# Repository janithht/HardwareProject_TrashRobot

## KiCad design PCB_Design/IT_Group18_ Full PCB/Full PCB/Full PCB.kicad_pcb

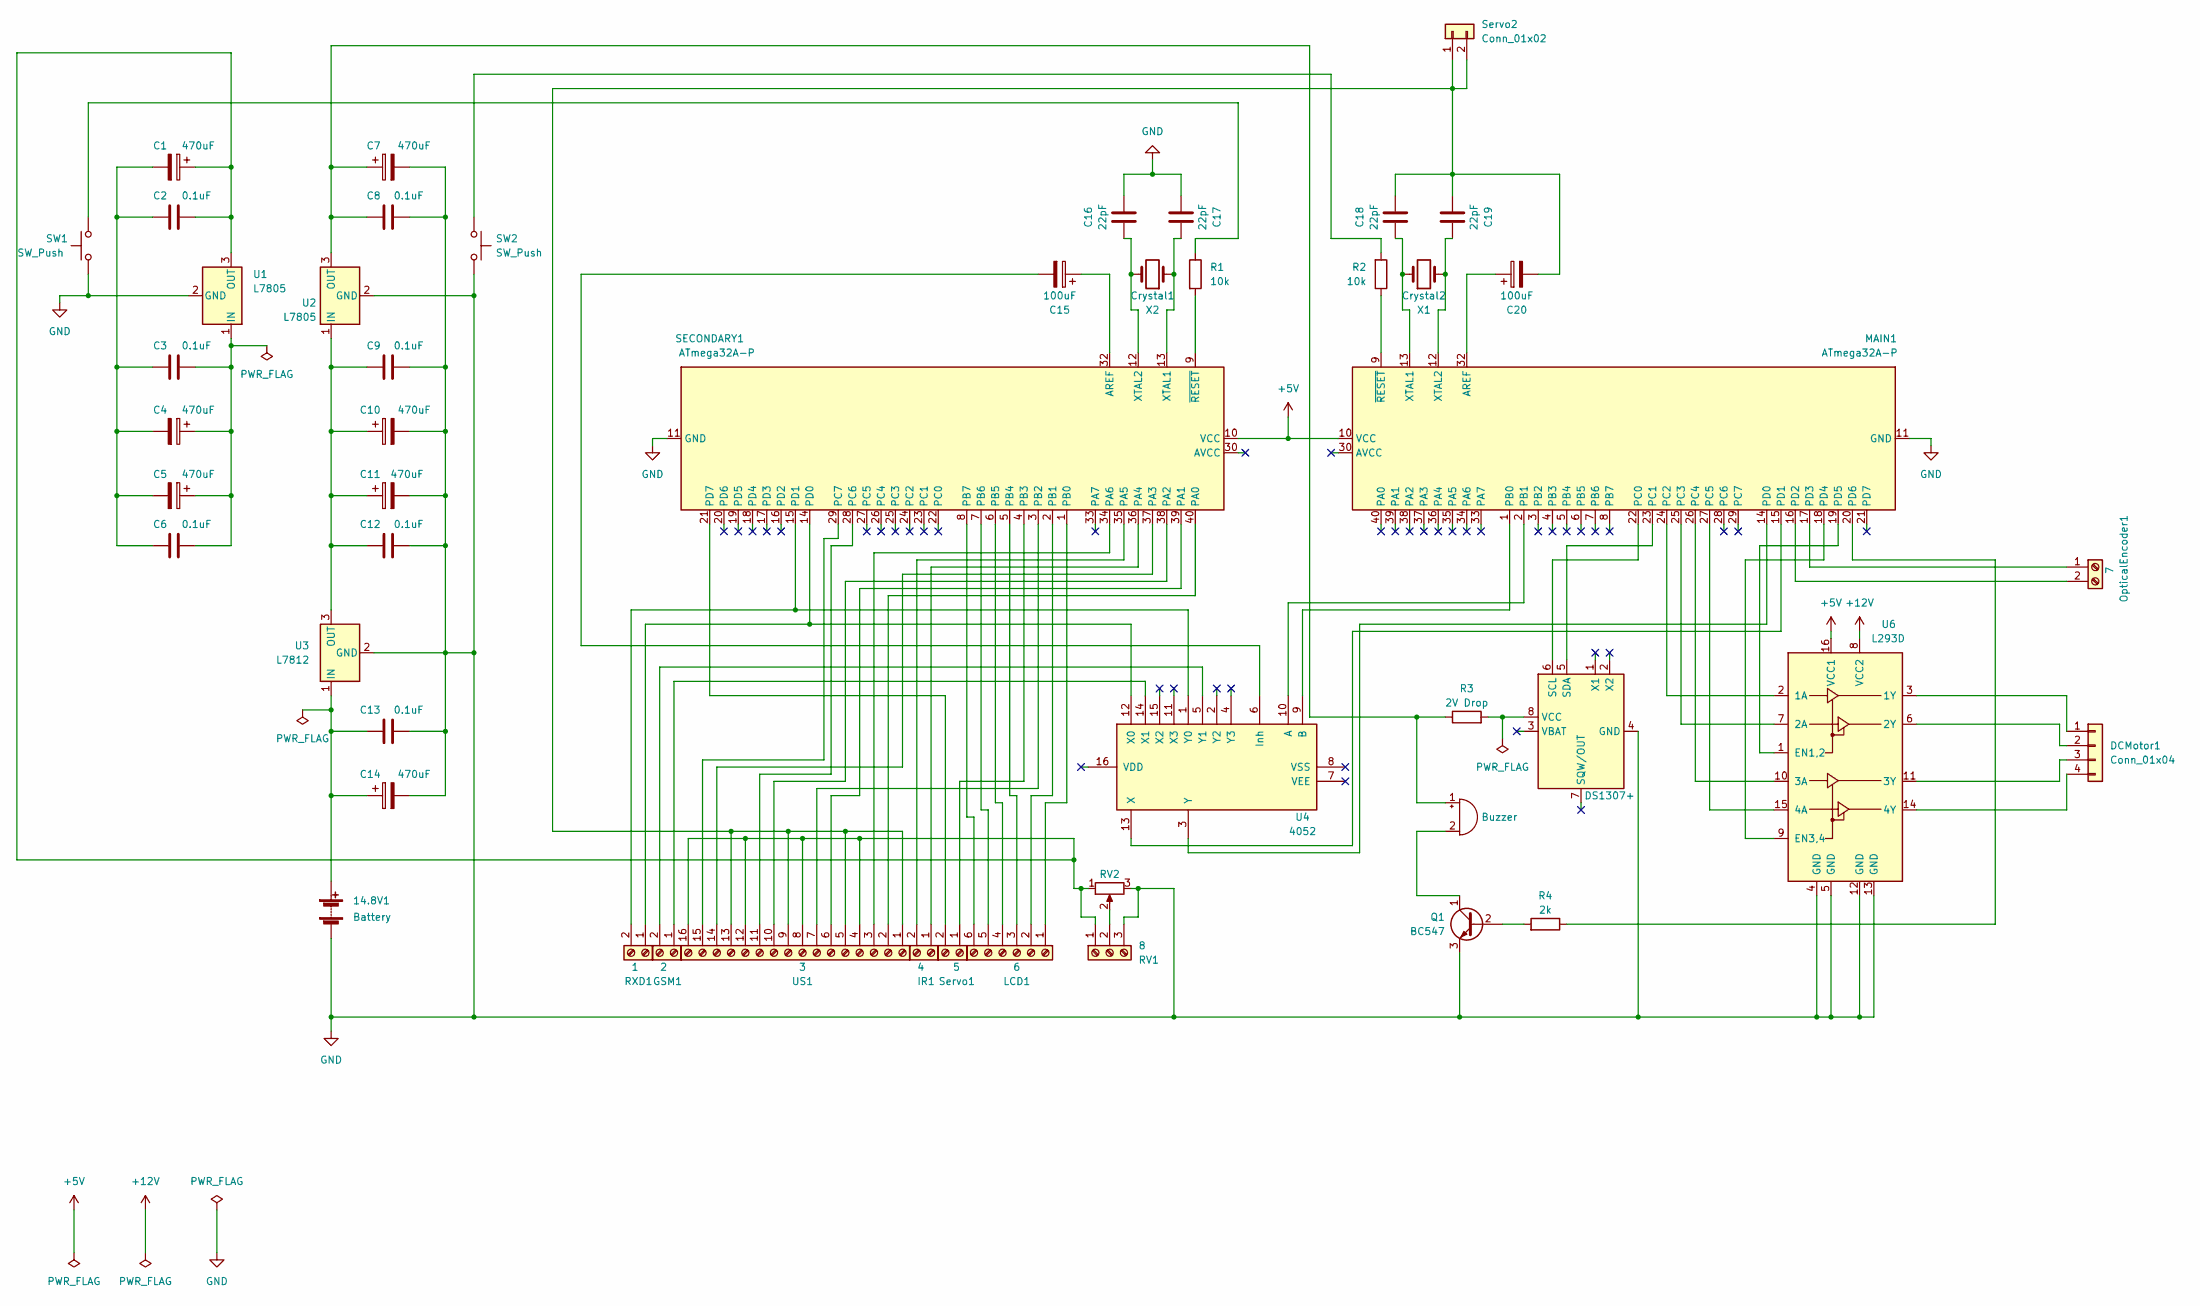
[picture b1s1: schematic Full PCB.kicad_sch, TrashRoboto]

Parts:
14.8V1: Battery; BatteryHolder_Bulgin_BX0036_1xC
BZ1: Buzzer; Buzzer_12x9.5RM7.6
C1, C4, C5, C7, C10, C11, C14: 470uF; CP_Radial_D5.0mm_P2.50mm
C2, C3, C6, C8, C9, C12, C13: 0.1uF; CP_Radial_D5.0mm_P2.50mm
C15, C20: 100uF; CP_Radial_D5.0mm_P2.50mm
C16, C17, C18, C19: 22pF; CP_Radial_D5.0mm_P2.50mm
Crystal1: X2; Crystal_HC52-U_Vertical
Crystal2: X1; Crystal_HC52-U_Vertical
DCMotor1: Conn_01x04; PinSocket_1x04_P2.54mm_Vertical
GSM1: 2; TerminalBlock_Dinkle_DT-55-B01X-02_P10.00mm
IR1: 4; TerminalBlock_Dinkle_DT-55-B01X-02_P10.00mm
LCD1: 6; TerminalBlock_Dinkle_DT-55-B01X-06_P10.00mm
MAIN1: ATmega32A-P; DIP-40_W15.24mm
OpticalEncoder1: 7; TerminalBlock_Dinkle_DT-55-B01X-02_P10.00mm
Q1: BC547; TO-92_Inline
R1, R2: 10k; R_Axial_DIN0207_L6.3mm_D2.5mm_P10.16mm_Horizontal
R3: 2V Drop; R_Axial_DIN0207_L6.3mm_D2.5mm_P10.16mm_Horizontal
R4: 2k; R_Axial_DIN0207_L6.3mm_D2.5mm_P10.16mm_Horizontal
RV1: 8; TerminalBlock_Dinkle_DT-55-B01X-03_P10.00mm
RV2: R_Potentiometer; Potentiometer_Runtron_RM-065_Vertical
RXD1: 1; TerminalBlock_Dinkle_DT-55-B01X-02_P10.00mm
SECONDARY1: ATmega32A-P; DIP-40_W15.24mm
SW1, SW2: SW_Push; SW_PUSH_6mm_H5mm
Servo1: 5; TerminalBlock_Dinkle_DT-55-B01X-02_P10.00mm
Servo2: Conn_01x02; PinSocket_1x02_P2.54mm_Vertical
U1, U2: L7805; TO-220-3_Vertical
U3: L7812; TO-220-3_Vertical
U4: 4052; DIP-16_W7.62mm
U5: DS1307+; DIP-8_W7.62mm
U6: L293D; DIP-16_W7.62mm
US1: 3; TerminalBlock_Dinkle_DT-55-B01X-16_P10.00mm

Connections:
+5V: MAIN1.10 (VCC), SECONDARY1.10 (VCC), U6.16 (VCC1)
+12V: U6.8 (VCC2)
GND: 14.8V1.2 (-), C7.2, C8.2, C9.2, C10.2, C11.2, C12.2, C13.2, C14.2, C16.2, C17.1, MAIN1.11 (GND), MAIN1.31 (GND), Q1.3 (E), RV1.3, RV2.3, SECONDARY1.11 (GND), SECONDARY1.31 (GND), SW1.2, SW2.2, U1.2 (GND), U2.2 (GND), U3.2 (GND), U5.4 (GND), U6.4 (GND), U6.5 (GND), U6.12 (GND), U6.13 (GND)
unnamed: 14.8V1.1 (+), C13.1, C14.1, U3.1 (IN)
unnamed: BZ1.1 (-), C7.1, C8.1, R3.1, U2.3 (OUT)
unnamed: BZ1.2 (+), Q1.1 (C)
unnamed: C1.2, C2.2, C3.2, C4.2, C5.2, C6.2
unnamed: C3.1, C4.1, C5.1, C6.1, U1.1 (IN)
unnamed: C9.1, C10.1, C11.1, C12.1, U2.1 (IN), U3.3 (OUT)
unnamed: C15.1, SECONDARY1.32 (AREF)
unnamed: C15.2, U4.6 (Inh)
unnamed: C16.1, Crystal1.2, SECONDARY1.12 (XTAL2)
unnamed: C17.2, Crystal1.1, SECONDARY1.13 (XTAL1)
unnamed: C18.1, C19.2, C20.2, Servo2.1, Servo2.2, US1.1, US1.5, US1.9, US1.13
unnamed: C18.2, Crystal2.1, MAIN1.13 (XTAL1)
unnamed: C19.1, Crystal2.2, MAIN1.12 (XTAL2)
unnamed: C20.1, MAIN1.32 (AREF)
unnamed: DCMotor1.1, U6.3 (1Y)
unnamed: DCMotor1.2, U6.6 (2Y)
unnamed: DCMotor1.3, U6.11 (3Y)
unnamed: DCMotor1.4, U6.14 (4Y)
unnamed: GSM1.1, U4.14 (X1)
unnamed: GSM1.2, U4.5 (Y1)
unnamed: IR1.1, SECONDARY1.36 (PA4)
unnamed: IR1.2, SECONDARY1.35 (PA5)
unnamed: MAIN1.1 (PB0), U4.9 (B)
unnamed: MAIN1.2 (PB1), U4.10 (A)
unnamed: MAIN1.9 (~RESET), R2.1
unnamed: MAIN1.14 (PD0), U4.3 (Y)
unnamed: MAIN1.15 (PD1), U4.13 (X)
unnamed: MAIN1.16 (PD2), OpticalEncoder1.2
unnamed: MAIN1.17 (PD3), OpticalEncoder1.1
unnamed: MAIN1.18 (PD4), U6.9 (EN3,4)
unnamed: MAIN1.19 (PD5), U6.1 (EN1,2)
unnamed: MAIN1.20 (PD6), R4.1
unnamed: MAIN1.22 (PC0), U5.6 (SCL)
unnamed: MAIN1.23 (PC1), U5.5 (SDA)
unnamed: MAIN1.24 (PC2), U6.2 (1A)
unnamed: MAIN1.25 (PC3), U6.7 (2A)
unnamed: MAIN1.26 (PC4), U6.10 (3A)
unnamed: MAIN1.27 (PC5), U6.15 (4A)
unnamed: Q1.2 (B), R4.2
unnamed: R1.1, SW1.1
unnamed: R1.2, SECONDARY1.9 (~RESET)
unnamed: R2.2, SW2.1
unnamed: R3.2, U5.8 (VCC)
unnamed: C1.1, C2.1, RV1.1, RV2.1, U1.3 (OUT), US1.4, US1.8, US1.12, US1.16
unnamed: RV1.2, RV2.2
unnamed: RXD1.1, SECONDARY1.14 (PD0), U4.12 (X0)
unnamed: RXD1.2, SECONDARY1.15 (PD1), U4.1 (Y0)
unnamed: LCD1.1, SECONDARY1.1 (PB0)
unnamed: LCD1.2, SECONDARY1.2 (PB1)
unnamed: SECONDARY1.3 (PB2), US1.7
unnamed: SECONDARY1.4 (PB3), Servo1.1
unnamed: LCD1.3, SECONDARY1.5 (PB4)
unnamed: LCD1.4, SECONDARY1.6 (PB5)
unnamed: LCD1.5, SECONDARY1.7 (PB6)
unnamed: LCD1.6, SECONDARY1.8 (PB7)
unnamed: SECONDARY1.21 (PD7), Servo1.2
unnamed: SECONDARY1.28 (PC6), US1.11
unnamed: SECONDARY1.29 (PC7), US1.15
unnamed: SECONDARY1.34 (PA6), US1.3
unnamed: SECONDARY1.37 (PA3), US1.14
unnamed: SECONDARY1.38 (PA2), US1.10
unnamed: SECONDARY1.39 (PA1), US1.6
unnamed: SECONDARY1.40 (PA0), US1.2

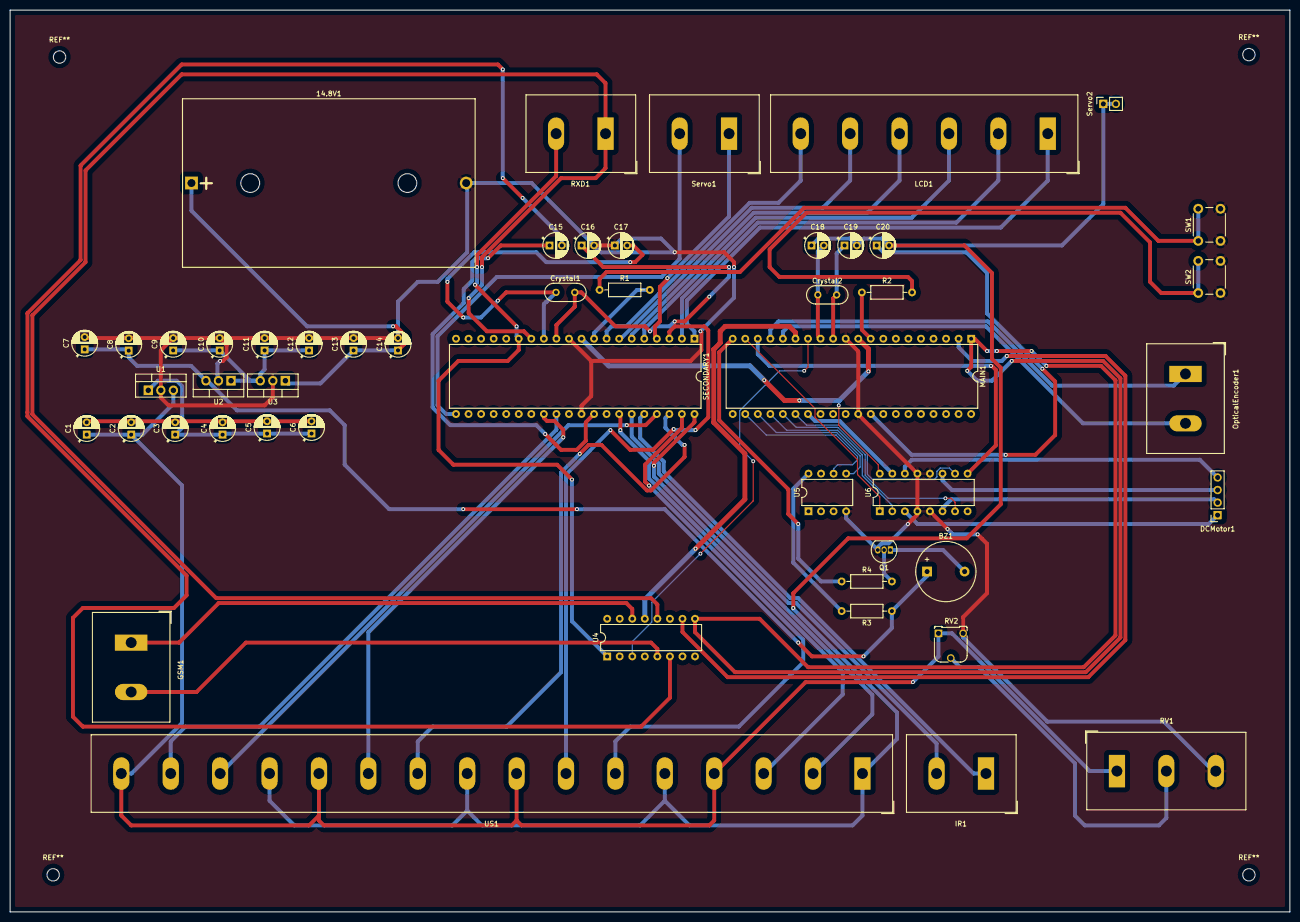
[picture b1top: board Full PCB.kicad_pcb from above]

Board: 2 copper layers, 259.0 x 182.5 mm, 50 parts (0 on the bottom side), 65 nets.

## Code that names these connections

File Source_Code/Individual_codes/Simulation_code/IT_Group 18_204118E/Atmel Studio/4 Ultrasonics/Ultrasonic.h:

#ifndef ULTRASONIC_H_
#define ULTRASONIC_H_

#define US1_TRIG_POS PA0         // Trigger pin on PA0
#define US1_ECHO_POS PA6         // Echo pin on PA6

#define US3_TRIG_POS PA2         // Trigger pin on PA2
#define US3_ECHO_POS PC6         // Echo pin on PA6

#define US2_TRIG_POS PA1        // Trigger pin on PA1
#define US2_ECHO_POS PB2         // Echo pin on PB2

#define US4_TRIG_POS PA3        // Trigger pin on PA3
#define US4_ECHO_POS PC7         // Echo pin on PC7

#define	US_NO_OBSTACLE	-2

// Function Prototypes
void HCSR04Init();
void HCSR04Trigger1();
void HCSR04Trigger2();
uint16_t GetPulseWidth1();
uint16_t GetPulseWidth2();
void HCSR04Trigger3();
void HCSR04Trigger4();
uint16_t GetPulseWidth3();
uint16_t GetPulseWidth4();

void HCSR04Init()						// Ultrasonic sensor initialization
{
	DDRA|=(1<<US1_TRIG_POS);			// Trigger pin as output
	DDRA|=(1<<US2_TRIG_POS);
	DDRA|=(1<<US3_TRIG_POS);			// Trigger pin as output
	DDRA|=(1<<US4_TRIG_POS);
}

void HCSR04Trigger1()					// Trigger pulse
{
	PORTA |= (1<<US1_TRIG_POS);		//high
	_delay_us(15);						//wait 15uS
	PORTA &= ~(1<<US1_TRIG_POS);		//low
}

void HCSR04Trigger2()					// Trigger pulse
{
	PORTA |= (1<<US2_TRIG_POS);		//high
	_delay_us(15);						//wait 15uS
	PORTA &= ~(1<<US2_TRIG_POS);		//low
}

uint16_t GetPulseWidth1()				// Measure the pulse duration
{
	uint32_t i,result;

	for(i=0;i<600000;i++)				// Checking whether ultrasonic sensor is working
	{
		if(!(PINA & (1<<US1_ECHO_POS)))
		continue;						//Line is still low
		else
		break;							//High edge detected
	}

	
	TCCR1A=0X00;
	TCCR1B=(1<<CS11);					// Resolution of the timer
	TCNT1=0x00;							// Start counting time

	for(i=0;i<600000;i++)				// Almost 40 milliseconds
	{
		if(PINA & (1<<US1_ECHO_POS))
		{
			if(TCNT1 > 60000)
			break;						// No object in the range
			else
			continue;
		}
		else
		break;
	}

	if(i==600000)
	return US_NO_OBSTACLE;				//Time out

	result=TCNT1;						//Falling edge found
	
	TCCR1B=0x00;						//Stop Timer

	if(result > 60000)
	return US_NO_OBSTACLE;				//No obstacle
	else
	return (result>>1);
}

uint16_t GetPulseWidth2()				// Measure the pulse duration
{
	uint32_t i,result;

	for(i=0;i<600000;i++)				// Checking whether ultrasonic sensor is working
	{
		if(!(PINB & (1<<US2_ECHO_POS)))
		continue;						//Line is still low
		else
		break;							//High edge detected
	}

	
	TCCR1A=0X00;
	TCCR1B=(1<<CS11);					// Resolution of the timer
	TCNT1=0x00;							// Start counting time

	for(i=0;i<600000;i++)				// Almost 40 milliseconds
	{
		if(PINB & (1<<US2_ECHO_POS))
		{
			if(TCNT1 > 60000)
			break;						// No object in the range
			else
			continue;
		}
		else
		break;
	}

	if(i==600000)
	return US_NO_OBSTACLE;				//Time out

	result=TCNT1;						//Falling edge found
	
	TCCR1B=0x00;						//Stop Timer

	if(result > 60000)
	return US_NO_OBSTACLE;				//No obstacle
	else
	return (result>>1);
}


void HCSR04Trigger3()					// Trigger pulse
{
	PORTA |= (1<<US3_TRIG_POS);		//high
	_delay_us(15);						//wait 15uS
	PORTA &= ~(1<<US3_TRIG_POS);		//low
}

void HCSR04Trigger4()					// Trigger pulse
{
	PORTA |= (1<<US4_TRIG_POS);		//high
	_delay_us(15);						//wait 15uS
	PORTA &= ~(1<<US4_TRIG_POS);		//low
}

uint16_t GetPulseWidth3()				// Measure the pulse duration
{
	uint32_t i,result;

	for(i=0;i<600000;i++)				// Checking whether ultrasonic sensor is working
	{
		if(!(PINC & (1<<US3_ECHO_POS)))
		continue;						//Line is still low
		else
		break;							//High edge detected
	}

	
	TCCR1A=0X00;
	TCCR1B=(1<<CS11);					// Resolution of the timer
	TCNT1=0x00;							// Start counting time

	for(i=0;i<600000;i++)				// Almost 40 milliseconds
	{
		if(PINC & (1<<US3_ECHO_POS))
		{
			if(TCNT1 > 60000)
			break;						// No object in the range
			else
			continue;
		}
		else
		break;
	}

	if(i==600000)
	return US_NO_OBSTACLE;				//Time out

	result=TCNT1;						//Falling edge found
	
	TCCR1B=0x00;						//Stop Timer

	if(result > 60000)
	return US_NO_OBSTACLE;				//No obstacle
	else
	return (result>>1);
}

uint16_t GetPulseWidth4()				// Measure the pulse duration
{
	uint32_t i,result;

	for(i=0;i<600000;i++)				// Checking whether ultrasonic sensor is working
	{
		if(!(PINC & (1<<US4_ECHO_POS)))
		continue;						//Line is still low
		else
		break;							//High edge detected
	}

	
	TCCR1A=0X00;
	TCCR1B=(1<<CS11);					// Resolution of the timer
	TCNT1=0x00;							// Start counting time

	for(i=0;i<600000;i++)				// Almost 40 milliseconds
	{
		if(PINC & (1<<US4_ECHO_POS))
		{
			if(TCNT1 > 60000)
			break;						// No object in the range
			else
			continue;
		}
		else
		break;
	}

	if(i==600000)
	return US_NO_OBSTACLE;				//Time out

	result=TCNT1;						//Falling edge found
	
	TCCR1B=0x00;						//Stop Timer

	if(result > 60000)
	return US_NO_OBSTACLE;				//No obstacle
	else
	return (result>>1);
}

#endif /* ULTRASONIC_H_ */

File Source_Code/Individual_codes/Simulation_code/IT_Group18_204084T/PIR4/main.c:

#include <avr/io.h>
#define F_CPU 16000000UL

int main(void)
{
   DDRB = DDRB | (1<<3);		//Make PB3 as output pin
   DDRD = DDRD | (1<<7);		//Make PD7 as output pin
   DDRA = DDRA & (~(1<<4));		//Make PA4 as input pin
   DDRA = DDRA & (~(1<<5));		//Make PA5 as input pin
   
    while (1) 
    {
		if (PINA & (1<<4))
		{
			PORTB = PORTB | (1<<3);
		}
		else
		{
			PORTB = PORTB & (~(1<<3));
		}
		
		if (PINA & (1<<5))
		{
			PORTD = PORTD | (1<<7);
		}
		else
		{
			PORTD = PORTD & (~(1<<7));
		}
		
    }
}

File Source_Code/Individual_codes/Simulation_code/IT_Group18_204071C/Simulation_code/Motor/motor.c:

#include <avr/io.h>
#include <avr/interrupt.h>

#include "motor.h"



void MotorInit()
{

	//set up pwm for speed control - PWM Phase Correct - 8 bit - Inverted

	TCCR1A=(1<<COM1A1)|(1<<COM1B1)|(1<<WGM10); 


	//clk=fcpu/64

	TCCR1B=(1<<CS11)|(1<<CS10);

	//Set the corresponding port pin to output

	DDR(OC1A_PORT)|=(1<<OC1A_PIN);
	DDR(OC1B_PORT)|=(1<<OC1B_PIN);

	//Set the direction control PINs to OUT
	DDRC|=0X3C;	//PC2 to PC5 as output

}


void MotorA(uint8_t dir,uint8_t speed)
{
	//Direction
	if(dir == MOTOR_STOP)
	{
		PORTC&=(~(1<<PC2));
		PORTC&=(~(1<<PC3));
	}

	else if(dir == MOTOR_CCW)
	{
		PORTC&=(~(1<<PC2));
		PORTC|=(1<<PC3);
	}
	else if(dir == MOTOR_CW)
	{
		PORTC&=(~(1<<PC3));
		PORTC|=(1<<PC2);
	}

	//Speed
	uint8_t sreg=SREG; //store SREG value
	cli();   //Disable Interrupts during times sequence

	OCR1A=speed;

	SREG=sreg;  //Restore SREG value(I-bit)
}


void MotorB(uint8_t dir,uint8_t speed)
{
	//Direction
	if(dir == MOTOR_STOP)
	{
		PORTC&=(~(1<<PC4));
		PORTC&=(~(1<<PC5));
	}

	else if(dir == MOTOR_CCW)
	{
		PORTC&=(~(1<<PC4)); //Define pull ups and set output low
		PORTC|=(1<<PC5);  //Define pull ups and set output high
	}
	else if(dir == MOTOR_CW)
	{
		PORTC&=(~(1<<PC5));
		PORTC|=(1<<PC4);
	}

	//Speed
	uint8_t sreg=SREG;
	cli();

	OCR1B=speed;

	SREG=sreg;
}
	

	

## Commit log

2023-01-05 Pushing to Git Repo
